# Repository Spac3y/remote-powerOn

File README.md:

# remote-powerOn

Remotely power on a PC (or any device with a momentary power-button header)
from Discord, using a Raspberry Pi and a small custom PCB.

Send `?on` in a private Discord channel and a Raspberry Pi pulses a GPIO pin,
which drives a transistor-switched relay/output on the custom board to
simulate a momentary press of the target device's power-button header. The
bot connects outbound-only via Discord's Gateway API, so there's no port
forwarding or public IP exposure of the Pi.

## Structure

- **`code/`** — the Discord bot (Python, `discord.py` + `gpiozero`) that
  runs on the Pi and drives the GPIO pin. See `code/README.md` for setup,
  Discord bot configuration, and systemd install instructions.
- **`kicad/`** — KiCad schematic/PCB design for the driver board that sits
  between the Pi's GPIO pin and the target device's power-button header. See
  `kicad/changes.md` for the design change log.

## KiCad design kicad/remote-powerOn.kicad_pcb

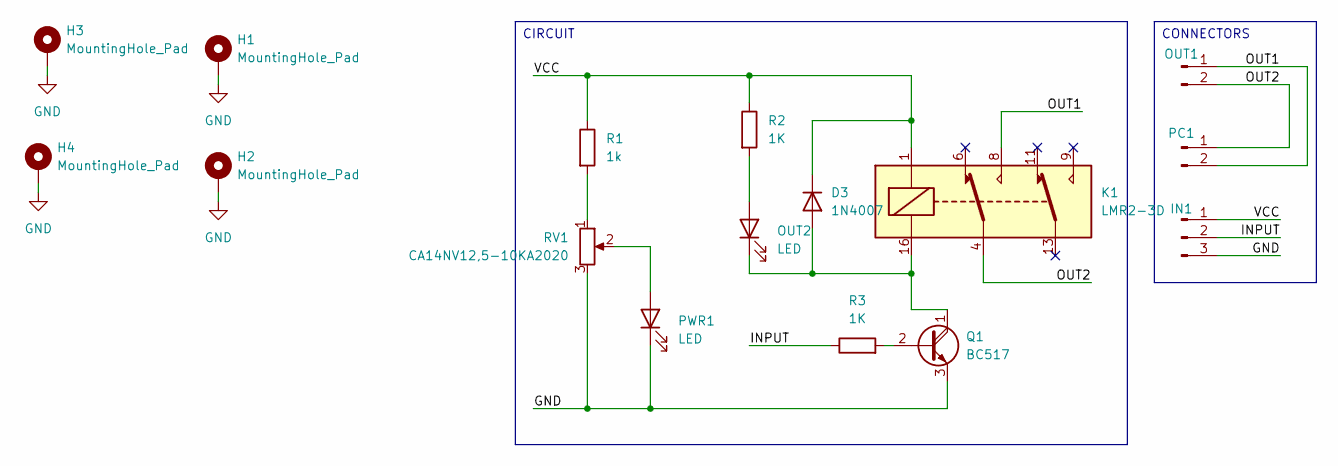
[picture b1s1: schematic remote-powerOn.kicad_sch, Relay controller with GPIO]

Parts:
D3: 1N4007; D_DO-41_SOD81_P10.16mm_Horizontal
H1, H2, H3, H4: MountingHole_Pad; MountingHole_2.7mm_M2.5_DIN965_Pad
IN1: Conn_01x03_Pin; PinHeader_1x03_P2.54mm_Vertical
K1: LMR2-3D
OUT1: Conn_01x02_Pin; PinHeader_1x02_P2.54mm_Vertical
OUT2: LED; LED_D5.0mm
PC1: Conn_01x02_Pin; PinHeader_1x02_P2.54mm_Vertical
PWR1: LED; LED_D5.0mm
Q1: BC517; TO-92_Inline
R1: 1k; R_Axial_DIN0207_L6.3mm_D2.5mm_P10.16mm_Horizontal
R2, R3: 1K; R_Axial_DIN0207_L6.3mm_D2.5mm_P10.16mm_Horizontal
RV1: CA14NV12,5-10KA2020; Potentiometer_ACP_CA14V-15_Vertical_Hole

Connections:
/INPUT: IN1.2, R3.1
/OUT1: K1.8, OUT1.1, PC1.2
/OUT2: K1.4, OUT1.2, PC1.1
/VCC: D3.1 (K), IN1.1, K1.1, R1.1, R2.1
GND: H1.1 (1_1), H2.1 (1_1), H3.1 (1_1), H4.1 (1_1), IN1.3, PWR1.1 (K), Q1.3 (E), RV1.3
unnamed: D3.2 (A), K1.16, OUT2.1 (K), Q1.1 (C)
unnamed: OUT2.2 (A), R2.2
unnamed: PWR1.2 (A), RV1.2
unnamed: Q1.2 (B), R3.2
unnamed: R1.2, RV1.1

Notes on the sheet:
CIRCUIT
CONNECTORS

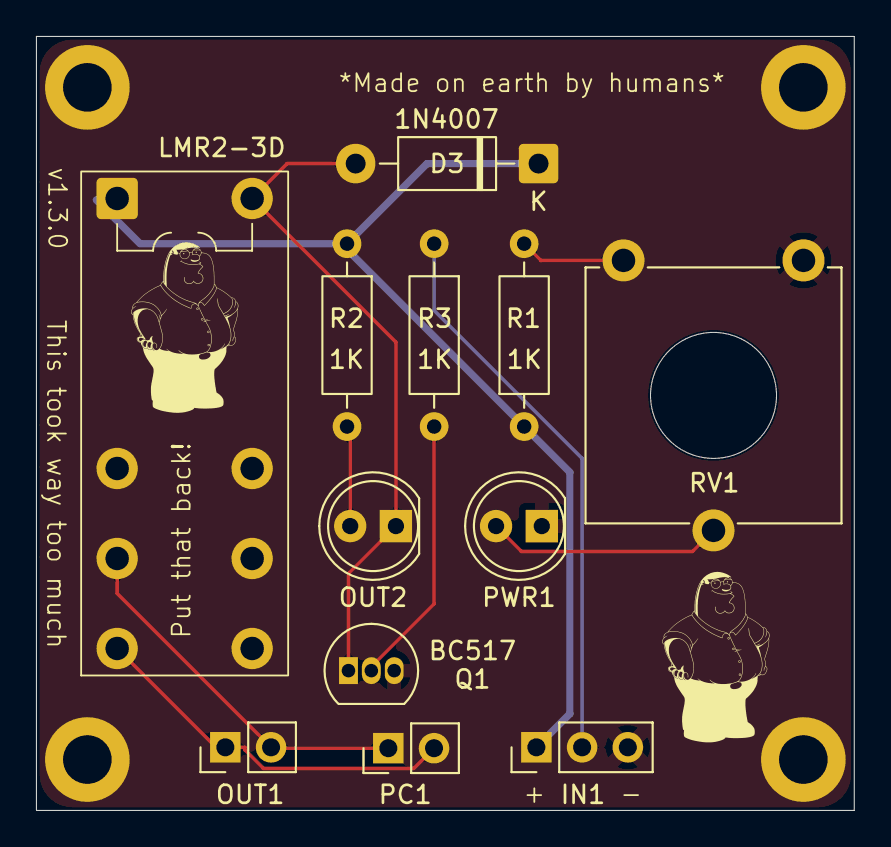
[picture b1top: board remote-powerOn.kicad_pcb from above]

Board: 2 copper layers, 45.4 x 43.0 mm, 18 parts (1 on the bottom side), 10 nets.

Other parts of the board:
Peter: LOGO; Peter_Image
refer2: LOGO; smth

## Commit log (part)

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2026-06-05 init
2026-06-09 create changes.md update pcb
